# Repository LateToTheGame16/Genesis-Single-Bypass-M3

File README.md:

# Sega Genesis Model 3 Stereo Mod
Restore stereo audio on a Sega Model 3. Only three wires to solder. Composite video still works! Only usable on a Model 3 Genesis.
This is a redesign of the fantastic 3bp from dbElectronics and Tian Feng. The goal of this project was to minimize wires to only do the audio bypass.

# Installation Instructions
Currently I suggest using the Audio installation instructions from https://github.com/zaxour/TripleBypassV2Plus
The 32X audio is taken from the cart connector. The audio is output to the Genesis Mini-DIN.
Solder wires for Audio Left, Audio Right, PSG taken from the top side of the Genesis motherboard.
# Design Files
The designs are done with Kicad 6.0. The designs were done from scratch and are native to Kicad. 
The schematic uses the same values as https://github.com/tianfeng33/triple-bypass-Version-2. 
The mechanicals changed to ease installation. 
# Change Log from V2
  - Schematics and Layout redrawn from scratch in Kicad. 
  - Only three wires need to be soldered. Video signals are not touched.

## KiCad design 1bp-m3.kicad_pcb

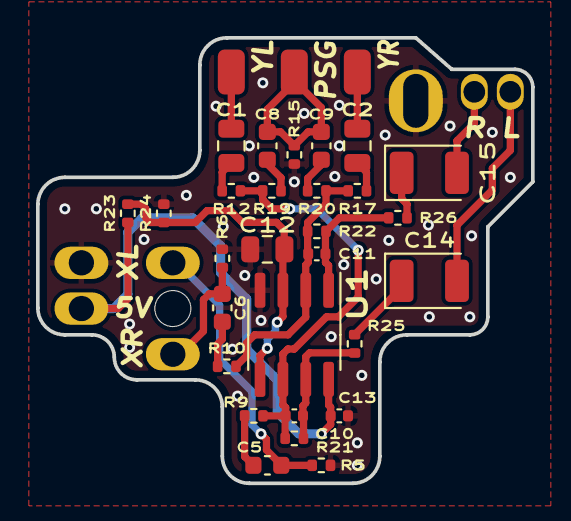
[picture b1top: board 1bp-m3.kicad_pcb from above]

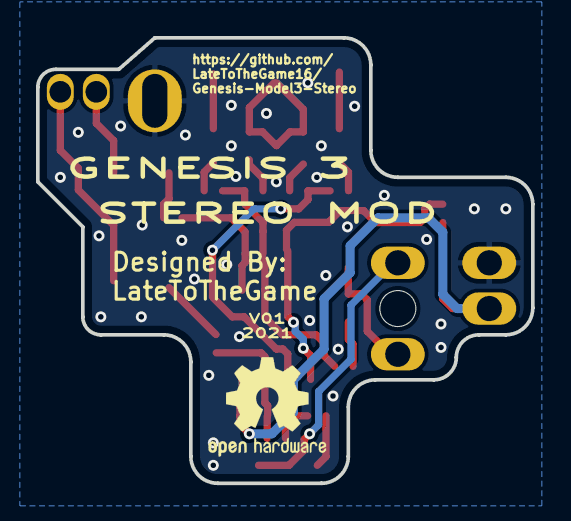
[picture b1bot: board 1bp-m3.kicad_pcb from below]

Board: 2 copper layers, 27.5 x 24.8 mm, 34 parts (2 on the bottom side), 22 nets.

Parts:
C1, C2, C12: 10uF; C_0805_2012Metric
C5, C6, C8, C9: 1uF; C_0603_1608Metric
C10, C11: 150pF; C_0402_1005Metric
C13: 0.1uF; C_0402_1005Metric
C14, C15: 47uF; CP_EIA-3528-21_Kemet-B
J1: TCS7913-43; MiniDIN_TCS7913-43
LOGO1: Logo_Open_Hardware_Small; OSHW-Logo2_7.3x6mm_SilkScreen
P7, P8, P13: TP_50; TestPoint_Pad_1.5x1.5mm
P9: TP_50; PinHeader_2x03_P2.54mm_Vertical
R5, R6: 75R; R_0402_1005Metric
R9, R10, R19, R20: 210K; R_0402_1005Metric
R12, R17: 130K; R_0402_1005Metric
R15: 2K2; R_0402_1005Metric
R21, R22: 300K; R_0402_1005Metric
R23, R24: 10K; R_0402_1005Metric
R25, R26: 330R; R_0402_1005Metric
U1: TL972IDR; SOIC-8_3.9x4.9mm_P1.27mm

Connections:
+5V: C13.1, P9.3, R23.1, U1.8 (V+)
/Mega Amp/2V5: C12.2, R23.2, R24.1, U1.3 (+), U1.5 (+)
/Mega Amp/32X-LEFT-IN: C5.1, P9.2, R5.1
/Mega Amp/32X-RIGHT-IN: C6.1, P9.6, R6.1
/Mega Amp/L-CH: C10.1, R9.2, R12.1, R19.2, R21.1, U1.6 (-)
/Mega Amp/L-OUT: C10.2, R21.2, R25.1, U1.7
/Mega Amp/PSG: C8.1, C9.1, P13.1, R15.1
/Mega Amp/R-CH: C11.1, R10.2, R17.1, R20.2, R22.1, U1.2 (-)
/Mega Amp/R-OUT: C11.2, R22.2, R26.1, U1.1
/Mega Amp/YM-L: C1.1, P7.1
/Mega Amp/YM-R: C2.1, P8.1
/SL: C14.2, J1.8
/SR: C15.2, J1.9
GND: C12.1, C13.2, J1.SH (Shield), P9.1, R5.2, R6.2, R15.2, R24.2, U1.4 (V-)
unnamed: C1.2, R12.2
unnamed: C2.2, R17.2
unnamed: C5.2, R9.1
unnamed: C6.2, R10.1
unnamed: C8.2, R19.1
unnamed: C9.2, R20.1
unnamed: C14.1, R25.2
unnamed: C15.1, R26.2

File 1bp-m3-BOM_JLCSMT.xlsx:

Comment | Designator | Footprint | JLCPCB Part #（optional）
10uF | C1, C2, C12 | Capacitor_SMD:C_0805_2012Metric | C15850
1uF | C5, C6, C8, C9 | Capacitor_SMD:C_0603_1608Metric | C29936
150pF | C10, C11 | Capacitor_SMD:C_0402_1005Metric | C76951
0.1uF | C13 | Capacitor_SMD:C_0402_1005Metric | C1525
47uF | C14, C15 | Capacitor_Tantalum_SMD:CP_EIA-3528-21_Kemet-B | C22036
75R | R5, R6 | Resistor_SMD:R_0402_1005Metric | C25133
210K | R9, R10, R19, R20 | Resistor_SMD:R_0402_1005Metric | C58827
130K | R12, R17 | Resistor_SMD:R_0402_1005Metric | C52929
2K2 | R15 | Resistor_SMD:R_0402_1005Metric | C25879
300K | R21, R22 | Resistor_SMD:R_0402_1005Metric | C25774
10K | R23, R24 | Resistor_SMD:R_0402_1005Metric | C25744
330R | R25, R26 | Resistor_SMD:R_0402_1005Metric | C25102
TL972IDR | U1 | Package_SO:SOIC-8_3.9x4.9mm_P1.27mm | C46127

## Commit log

2022-01-27 initial upload
2022-01-27 Rename license to license.md
2022-01-31 updated silkscreen for OSHW
2022-06-28 export gerbers
    first fab run
2022-06-28 built by JLCPCB
    first build attempt
2025-02-09 Update README.md
    Deleted parts saying the board was untested. It has been tested and works.
    Added a link to zaxour github page because he has great installation guides.
2025-02-10 Saved in KiCad 8.0, fixed part descriptions
    Component descriptions were wrong. Parts said 0603 but were really a 0402 footprint. No real changes to schematic or pcb. Saving from KiCad 6 to KiCad 8 created lots of format changes.

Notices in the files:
1bp-m3.kicad_pcb:
Licensed under CERN OHL v.1.2
